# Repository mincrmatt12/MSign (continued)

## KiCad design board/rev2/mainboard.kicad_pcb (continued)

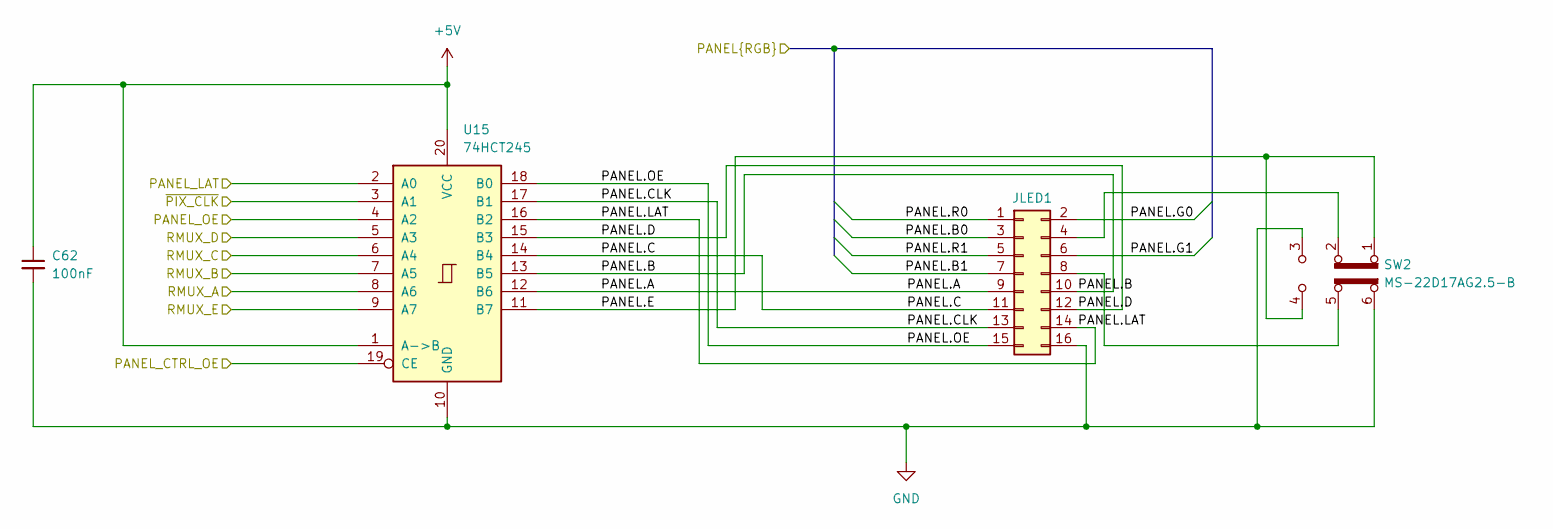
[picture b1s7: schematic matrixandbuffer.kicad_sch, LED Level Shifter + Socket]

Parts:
C62: 100nF; C_0402_1005Metric; Part CL05B104KB54PNC; LCSC C307331
JLED1: Conn_02x08_Counter_Clockwise; IDC-Header_2x08_P2.54mm_Vertical
SW2: MS-22D17AG2.5-B; SW-SMD_MS-22D17AG2.5; Part MS-22D17AG2.5-B; LCSC C20611671
U15: 74HCT245; TSSOP-20_4.4x6.5mm_P0.65mm; Part 74HCT245PW,118; LCSC C5980

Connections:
+5V: C62.1, U15.1 (A->B), U15.20 (VCC); also elsewhere on the board
/Decoder/PANELA.B0: JLED1.3; also elsewhere on the board
/Decoder/PANELA.B1: JLED1.7; also elsewhere on the board
/Decoder/PANELA.G0: JLED1.2; also elsewhere on the board
/Decoder/PANELA.G1: JLED1.6; also elsewhere on the board
/Decoder/PANELA.R0: JLED1.1; also elsewhere on the board
/Decoder/PANELA.R1: JLED1.5; also elsewhere on the board
/Decoder/PANEL_RGB_OE: U15.19 (CE); also elsewhere on the board
/Display MCU/PANEL_LAT: U15.2 (A0); also elsewhere on the board
/Display MCU/PANEL_OE: U15.4 (A2); also elsewhere on the board
/Display MCU/RMUX_A: U15.8 (A6); also elsewhere on the board
/Display MCU/RMUX_B: U15.7 (A5); also elsewhere on the board
/Display MCU/RMUX_C: U15.6 (A4); also elsewhere on the board
/Display MCU/RMUX_D: U15.5 (A3); also elsewhere on the board
/Display MCU/RMUX_E: U15.9 (A7); also elsewhere on the board
/Display MCU/~PIX_CLK: U15.3 (A1); also elsewhere on the board
/LED Connection A/PANEL.A: JLED1.9, U15.12 (B6)
/LED Connection A/PANEL.B: JLED1.10, U15.13 (B5)
/LED Connection A/PANEL.C: JLED1.11, U15.14 (B4)
/LED Connection A/PANEL.CLK: JLED1.13, U15.17 (B1)
/LED Connection A/PANEL.D: JLED1.12, U15.15 (B3)
/LED Connection A/PANEL.E: SW2.1 (A), SW2.4 (A), U15.11 (B7)
/LED Connection A/PANEL.LAT: JLED1.14, U15.16 (B2)
/LED Connection A/PANEL.OE: JLED1.15, U15.18 (B0)
GND: C62.2, JLED1.16, SW2.3 (C), SW2.6 (C), U15.10 (GND); also elsewhere on the board
unnamed: JLED1.4, SW2.2 (B)
unnamed: JLED1.8, SW2.5 (B)

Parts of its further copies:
C63: 100nF; C_0402_1005Metric; Part CL05B104KB54PNC; LCSC C307331
JLED2: Conn_02x08_Counter_Clockwise; IDC-Header_2x08_P2.54mm_Vertical
SW3: MS-22D17AG2.5-B; SW-SMD_MS-22D17AG2.5; Part MS-22D17AG2.5-B; LCSC C20611671
U16: 74HCT245; TSSOP-20_4.4x6.5mm_P0.65mm; Part 74HCT245PW,118; LCSC C5980

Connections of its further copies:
+5V: C63.1, U16.1 (A->B), U16.20 (VCC); also elsewhere on the board
/Decoder/PANELB.B0: JLED2.3; also elsewhere on the board
/Decoder/PANELB.B1: JLED2.7; also elsewhere on the board
/Decoder/PANELB.G0: JLED2.2; also elsewhere on the board
/Decoder/PANELB.G1: JLED2.6; also elsewhere on the board
/Decoder/PANELB.R0: JLED2.1; also elsewhere on the board
/Decoder/PANELB.R1: JLED2.5; also elsewhere on the board
/Decoder/PANEL_RGB_OE: U16.19 (CE); also elsewhere on the board
/Display MCU/PANEL_LAT: U16.2 (A0); also elsewhere on the board
/Display MCU/PANEL_OE: U16.4 (A2); also elsewhere on the board
/Display MCU/RMUX_A: U16.8 (A6); also elsewhere on the board
/Display MCU/RMUX_B: U16.7 (A5); also elsewhere on the board
/Display MCU/RMUX_C: U16.6 (A4); also elsewhere on the board
/Display MCU/RMUX_D: U16.5 (A3); also elsewhere on the board
/Display MCU/RMUX_E: U16.9 (A7); also elsewhere on the board
/Display MCU/~PIX_CLK: U16.3 (A1); also elsewhere on the board
/LED Connection B/PANEL.A: JLED2.9, U16.12 (B6)
/LED Connection B/PANEL.B: JLED2.10, U16.13 (B5)
/LED Connection B/PANEL.C: JLED2.11, U16.14 (B4)
/LED Connection B/PANEL.CLK: JLED2.13, U16.17 (B1)
/LED Connection B/PANEL.D: JLED2.12, U16.15 (B3)
/LED Connection B/PANEL.E: SW3.1 (A), SW3.4 (A), U16.11 (B7)
/LED Connection B/PANEL.LAT: JLED2.14, U16.16 (B2)
/LED Connection B/PANEL.OE: JLED2.15, U16.18 (B0)
GND: C63.2, JLED2.16, SW3.3 (C), SW3.6 (C), U16.10 (GND); also elsewhere on the board
unnamed: JLED2.4, SW3.2 (B)
unnamed: JLED2.8, SW3.5 (B)

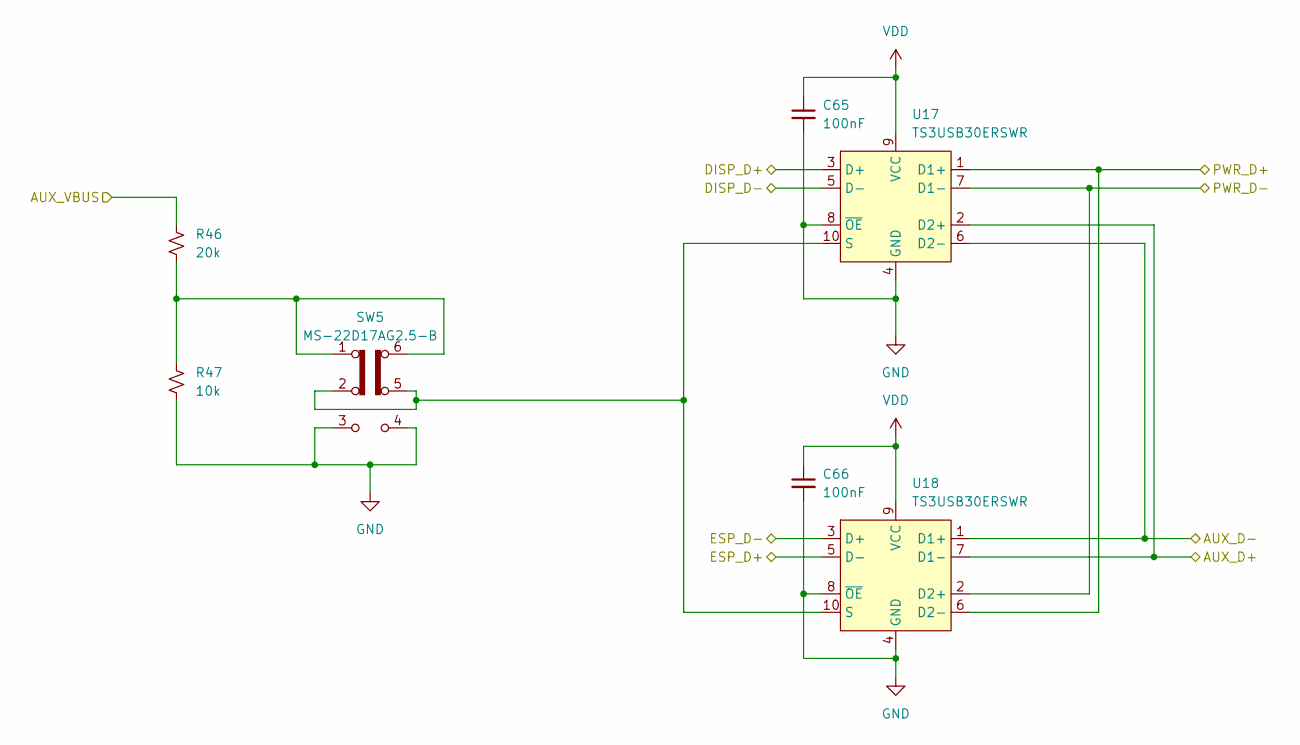
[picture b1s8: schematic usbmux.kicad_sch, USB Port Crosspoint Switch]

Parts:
C65, C66: 100nF; C_0402_1005Metric; Part CL05B104KB54PNC; LCSC C307331
R46: 20k; R_0603_1608Metric; Part 0603WAF2002T5E; LCSC C4184
R47: 10k; R_0805_2012Metric; Part 0805W8F1002T5E; LCSC C17414
SW5: MS-22D17AG2.5-B; SW-SMD_MS-22D17AG2.5; Part MS-22D17AG2.5-B; LCSC C20611671
U17, U18: TS3USB30ERSWR; UQFN-10_1.4x1.8mm_P0.4mm; Part TS3USB30ERSWR; LCSC C73880

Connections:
/Display MCU/USB_D+: U17.3 (D+); also elsewhere on the board
/Display MCU/USB_D-: U17.5 (D-); also elsewhere on the board
/Peripherals/AUX_USB_D+: U17.2 (D2+), U18.7 (D1-); also elsewhere on the board
/Peripherals/AUX_USB_D-: U17.6 (D2-), U18.1 (D1+); also elsewhere on the board
/Peripherals/AUX_USB_VBUS: R46.1; also elsewhere on the board
/Power/USB_D+: U17.1 (D1+), U18.6 (D2-); also elsewhere on the board
/Power/USB_D-: U17.7 (D1-), U18.2 (D2+); also elsewhere on the board
/USB Mux/ESP_D+: U18.5 (D-); also elsewhere on the board
/USB Mux/ESP_D-: U18.3 (D+); also elsewhere on the board
GND: C65.2, C66.2, R47.2, SW5.3 (C), SW5.4 (A), U17.4 (GND), U17.8 (~OE), U18.4 (GND), U18.8 (~OE); also elsewhere on the board
unnamed: R46.2, R47.1, SW5.1 (A), SW5.6 (C)
unnamed: SW5.2 (B), SW5.5 (B), U17.10 (S), U18.10 (S)
VDD: C65.1, C66.1, U17.9 (VCC), U18.9 (VCC); also elsewhere on the board

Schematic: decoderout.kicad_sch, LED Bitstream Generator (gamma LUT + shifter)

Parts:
C58, C59: 100nF; C_0402_1005Metric; Part CL05B104KB54PNC; LCSC C307331
R17, R24, R25, R26, R27, R28, R29, R30: 1k; R_0402_1005Metric; Part 0402WGF1001TCE; LCSC C11702
U11: IS61LV256AL; TSOP-28_L11.8-W8.0-P0.55-LS13.4-L; Part IS61LV256AL-10TLI; LCSC C412837
U12: 74AHCT595; TSSOP-16_4.4x5mm_P0.65mm; Part 74AHCT595T16-13; LCSC C460504

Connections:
+5V: C59.1, U12.10 (~SRCLR), U12.16 (VCC); also elsewhere on the board
/Decoder/MEMA_WE: U11.27 (~WE); also elsewhere on the board
/Decoder/MEM_A13: U11.21 (A10); also elsewhere on the board
/Decoder/MEM_IO: R17.2; also elsewhere on the board
/Decoder/Output Stage A/PIX_CNT_Q0: U11.26 (A13); also elsewhere on the board
/Decoder/Output Stage A/PIX_CNT_Q1: U11.25 (A8); also elsewhere on the board
/Decoder/Output Stage A/PIX_CNT_Q2: U11.24 (A9); also elsewhere on the board
/Decoder/Output Stage A/PIX_CNT_Q3: U11.23 (A11); also elsewhere on the board
/Decoder/Output Stage A/PIX_RGB_Q0: U11.1 (A14); also elsewhere on the board
/Decoder/Output Stage A/PIX_RGB_Q1: U11.2 (A12); also elsewhere on the board
/Decoder/PANELA.B0: U12.2 (QC); also elsewhere on the board
/Decoder/PANELA.B1: U12.5 (QF); also elsewhere on the board
/Decoder/PANELA.G0: U12.1 (QB); also elsewhere on the board
/Decoder/PANELA.G1: U12.4 (QE); also elsewhere on the board
/Decoder/PANELA.R0: U12.15 (QA); also elsewhere on the board
/Decoder/PANELA.R1: U12.3 (QD); also elsewhere on the board
/Decoder/PANEL_RGB_OE: U12.13 (~OE); also elsewhere on the board
/Decoder/PIX_CLK: U12.12 (RCLK); also elsewhere on the board
/Decoder/PIX_MEM_PA0: U11.10 (A0); also elsewhere on the board
/Decoder/PIX_MEM_PA1: U11.9 (A1); also elsewhere on the board
/Decoder/PIX_MEM_PA2: U11.8 (A2); also elsewhere on the board
/Decoder/PIX_MEM_PA3: U11.7 (A3); also elsewhere on the board
/Decoder/PIX_MEM_PA4: U11.6 (A4); also elsewhere on the board
/Decoder/PIX_MEM_PA5: U11.5 (A5); also elsewhere on the board
/Decoder/PIX_MEM_PA6: U11.4 (A6); also elsewhere on the board
/Decoder/PIX_MEM_PA7: U11.3 (A7); also elsewhere on the board
/Decoder/RGB_CLK: U12.11 (SRCLK); also elsewhere on the board
GND: C58.1, C59.2, R24.2, R25.2, R26.2, R27.2, R28.2, R29.2, R30.2, U11.14 (GND), U11.20 (~CE), U11.22 (~OE), U12.8 (GND); also elsewhere on the board
unnamed: R17.1, U11.11 (I/O0), U12.14 (SER)
unnamed: R24.1, U11.12 (I/O1)
unnamed: R25.1, U11.13 (I/O2)
unnamed: R26.1, U11.15 (I/O3)
unnamed: R27.1, U11.16 (I/O4)
unnamed: R28.1, U11.17 (I/O5)
unnamed: R29.1, U11.18 (I/O6)
unnamed: R30.1, U11.19 (I/O7)
VDD: C58.2, U11.28 (VDD); also elsewhere on the board

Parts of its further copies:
C60, C61: 100nF; C_0402_1005Metric; Part CL05B104KB54PNC; LCSC C307331
R32, R33, R34, R35, R36, R37, R38, R52: 1k; R_0402_1005Metric; Part 0402WGF1001TCE; LCSC C11702
U13: IS61LV256AL; TSOP-28_L11.8-W8.0-P0.55-LS13.4-L; Part IS61LV256AL-10TLI; LCSC C412837
U14: 74AHCT595; TSSOP-16_4.4x5mm_P0.65mm; Part 74AHCT595T16-13; LCSC C460504

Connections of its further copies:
+5V: C61.1, U14.10 (~SRCLR), U14.16 (VCC); also elsewhere on the board
/Decoder/MEMB_WE: U13.27 (~WE); also elsewhere on the board
/Decoder/MEM_A13: U13.21 (A10); also elsewhere on the board
/Decoder/MEM_IO: R52.2; also elsewhere on the board
/Decoder/Output Stage A/PIX_CNT_Q0: U13.26 (A13); also elsewhere on the board
/Decoder/Output Stage A/PIX_CNT_Q1: U13.25 (A8); also elsewhere on the board
/Decoder/Output Stage A/PIX_CNT_Q2: U13.24 (A9); also elsewhere on the board
/Decoder/Output Stage A/PIX_CNT_Q3: U13.23 (A11); also elsewhere on the board
/Decoder/Output Stage A/PIX_RGB_Q0: U13.1 (A14); also elsewhere on the board
/Decoder/Output Stage A/PIX_RGB_Q1: U13.2 (A12); also elsewhere on the board
/Decoder/PANELB.B0: U14.2 (QC); also elsewhere on the board
/Decoder/PANELB.B1: U14.5 (QF); also elsewhere on the board
/Decoder/PANELB.G0: U14.1 (QB); also elsewhere on the board
/Decoder/PANELB.G1: U14.4 (QE); also elsewhere on the board
/Decoder/PANELB.R0: U14.15 (QA); also elsewhere on the board
/Decoder/PANELB.R1: U14.3 (QD); also elsewhere on the board
/Decoder/PANEL_RGB_OE: U14.13 (~OE); also elsewhere on the board
/Decoder/PIX_CLK: U14.12 (RCLK); also elsewhere on the board
/Decoder/PIX_MEM_PB0: U13.10 (A0); also elsewhere on the board
/Decoder/PIX_MEM_PB1: U13.9 (A1); also elsewhere on the board
/Decoder/PIX_MEM_PB2: U13.8 (A2); also elsewhere on the board
/Decoder/PIX_MEM_PB3: U13.7 (A3); also elsewhere on the board
/Decoder/PIX_MEM_PB4: U13.6 (A4); also elsewhere on the board
/Decoder/PIX_MEM_PB5: U13.5 (A5); also elsewhere on the board
/Decoder/PIX_MEM_PB6: U13.4 (A6); also elsewhere on the board
/Decoder/PIX_MEM_PB7: U13.3 (A7); also elsewhere on the board
/Decoder/RGB_CLK: U14.11 (SRCLK); also elsewhere on the board
GND: C60.1, C61.2, R32.2, R33.2, R34.2, R35.2, R36.2, R37.2, R38.2, U13.14 (GND), U13.20 (~CE), U13.22 (~OE), U14.8 (GND); also elsewhere on the board
unnamed: R52.1, U13.11 (I/O0), U14.14 (SER)
unnamed: R32.1, U13.12 (I/O1)
unnamed: R33.1, U13.13 (I/O2)
unnamed: R34.1, U13.15 (I/O3)
unnamed: R35.1, U13.16 (I/O4)
unnamed: R36.1, U13.17 (I/O5)
unnamed: R37.1, U13.18 (I/O6)
unnamed: R38.1, U13.19 (I/O7)
VDD: C60.2, U13.28 (VDD); also elsewhere on the board

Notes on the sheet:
Gamma correction table (PIX_MEM)

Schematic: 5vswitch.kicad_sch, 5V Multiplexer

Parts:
C11: 1uF; C_0603_1608Metric; Part CL10A105KB8NNNC; LCSC C15849
C12, C15: 100nF; C_0402_1005Metric; Part CL05B104KB54PNC; LCSC C307331
C13: 2.2nF; C_0603_1608Metric; Part 0603B222K500NT; LCSC C1604
C14: 8.2nF; C_0603_1608Metric; Part 0603B822K500NT; LCSC C1322360
C16: 10uF; C_1206_3216Metric; Part CL31A106KBHNNNE; LCSC C13585
C17: 220uF; CP_Radial_D8.0mm_P3.50mm; Part ERS1VM221F12OT; LCSC C106697
Q1: WSD40120DN56G; DFN-8_L4.9-W6.0-P1.27-LS6.1-BL; Part WSD40120DN56G; LCSC C507088
Q2: 2N7002; SOT-23; Part 2N7002; LCSC C8545
R3: 10k; R_0402_1005Metric; Part 0402WGF1002TCE; LCSC C25744
R4: 510; R_0603_1608Metric; Part 0603WAF5100T5E; LCSC C23193
R5: 1.2k; R_0805_2012Metric; Part 0805W8F1201T5E; LCSC C17379
R6: 470k; R_0805_2012Metric; Part 0805W8F4703T5E; LCSC C17709
R7: 150k; R_0805_2012Metric; Part 0805W8F1503T5E; LCSC C17470
U3: TPS259472A; VQFN-10_L2.0-W2.0-P0.45-TL; Part TPS259472ARPWR; LCSC C3662789
U4: LM5050-1; TSOT-23-6; Part LM5050MKX-1/NOPB; LCSC C473393

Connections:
+5V: C16.1, C17.1, Q1.3 (D), R6.1, U3.6 (OUT), U4.6 (OUT); also elsewhere on the board
/Power MCU/DISC_5VREG: Q2.1 (G); also elsewhere on the board
/Power MCU/EN_5VREG: U4.3 (OFF); also elsewhere on the board
/Power MCU/EN_VBUS: R3.1, U3.1 (EN_UVLO); also elsewhere on the board
/Power MCU/VBUS_IMEAS: R5.1, U3.9 (ILM); also elsewhere on the board
/Power MCU/VBUS_PGOOD: U3.3 (PG); also elsewhere on the board
/Power/5V_REG: C15.1, Q1.1 (S), Q2.3 (D), U4.1 (VS), U4.4 (IN); also elsewhere on the board
/Power/VBUS: C11.1, C12.1, U3.5 (IN); also elsewhere on the board
GND: C11.2, C12.2, C13.2, C14.2, C15.2, C16.2, C17.2, R3.2, R4.2, R5.2, R7.2, U3.8 (GND), U4.2 (GND); also elsewhere on the board
unnamed: Q1.2 (G), U4.5 (GATE)
unnamed: Q2.2 (S), R4.1
unnamed: C13.1, U3.10 (ITIMER)
unnamed: R6.2, R7.1, U3.4 (PGTH)
unnamed: C14.1, U3.7 (dVdt)

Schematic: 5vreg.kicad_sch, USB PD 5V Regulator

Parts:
C18: 150uF; CP_Radial_D8.0mm_P3.50mm; Part ERS1VM151F12OT; LCSC C106696
C19, C20, C22: 4.7uF; C_1206_3216Metric; Part 1206B475K500NT; LCSC C29823
C21, C24, C25, C71: 100nF; C_0402_1005Metric; Part CL05B104KB54PNC; LCSC C307331
C23: 1uF; C_0603_1608Metric; Part CL10A105KB8NNNC; LCSC C15849
C26, C27, C28, C29, C30, C31, C32, C33: 47uF; C_1206_3216Metric; Part CL31A476MPHNNNE; LCSC C96123
L2: 1uH; L_Cenker_CKST1707; Part CKST1707-1uH/M; LCSC C5292052
NT1, NT2: NetTie_2; NetTie-2_SMD_Pad0.5mm
R8: 10k; R_0402_1005Metric; Part 0402WGF1002TCE; LCSC C25744
R9: 3.3k; R_0402_1005Metric; Part 0402WGF3301TCE; LCSC C25890
R10: 2.2; R_0603_1608Metric; Part 0603WAF220KT5E; LCSC C22939
TP7: TestPoint; TestPoint_Pad_D1.0mm
U5: SiC451; POWERPAK_MLP34-57_VIS; Part SIC451ED-T1-GE3; LCSC C1852144

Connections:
/Power MCU/5V_REG_SCL: U5.20 (SCL); also elsewhere on the board
/Power MCU/5V_REG_SDA: U5.19 (SDA); also elsewhere on the board
/Power MCU/5V_REG_SMBA: U5.18 (SALERT); also elsewhere on the board
/Power/5V Reg/VSEN+: NT1.1, U5.12 (VSEN+)
/Power/5V Reg/VSEN-: NT2.1, U5.11 (VSEN-)
/Power/5V_REG: C25.1, C26.1, C27.1, C28.1, C29.1, C30.1, C31.1, C32.1, C33.1, L2.2, NT1.2; also elsewhere on the board
/Power/VBUS: C18.1, C19.1, C20.1, C21.1, C71.1, U5.1 (PVIN), U5.23 (VIN); also elsewhere on the board
GND: C18.2, C19.2, C20.2, C21.2, C22.2, C23.2, C25.2, C26.2, C27.2, C28.2, C29.2, C30.2, C31.2, C32.2, C33.2, C71.2, NT2.2, R8.2, R9.2, TP7.1 (1_1), U5.7 (AGND), U5.15 (VSET), U5.21 (EN), U5.32 (PGND); also elsewhere on the board
unnamed: C24.2, R10.1
unnamed: R8.1, U5.14 (ADDR)
unnamed: R10.2, U5.6 (BOOT)
unnamed: C24.1, U5.4 (PHASE)
unnamed: C22.1, U5.24 (PVCC)
unnamed: R9.1, U5.17 (RT/SYNC)
unnamed: L2.1, U5.26 (SW)
unnamed: C23.1, U5.22 (VDD)

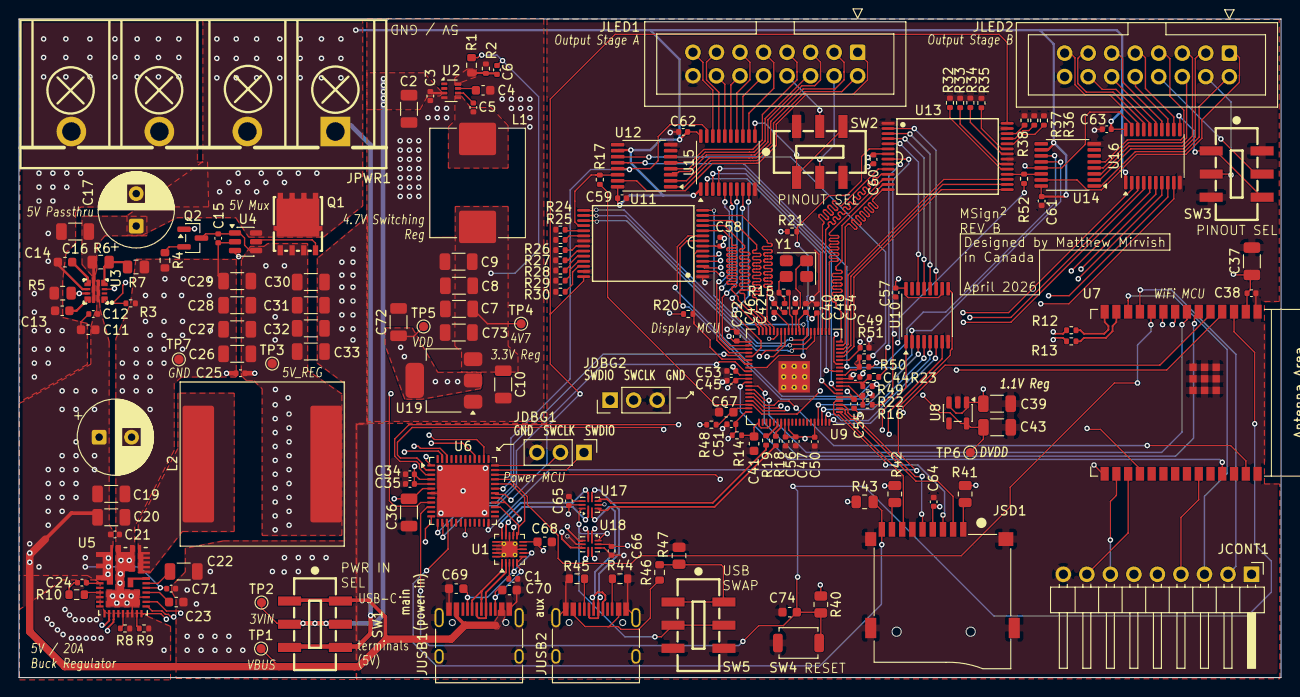
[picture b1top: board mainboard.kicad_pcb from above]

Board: 4 copper layers, 136.2 x 71.1 mm, 170 parts (0 on the bottom side), 189 nets.

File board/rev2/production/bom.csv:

Designator,Footprint,Quantity,Value,LCSC Part #
"C1, C12, C15, C21, C24, C25, C3, C34, C35, C38, C44, C45, C46, C47, C48, C49, C5, C50, C51, C52, C53, C54, C55, C56, C57, C58, C59, C60, C61, C62, C63, C64, C65, C66, C71",0402,35,100nF,C307331 
"C10, C16, C2, C37, C72",1206,5,10uF,C13585
"C11, C23, C68, C74",0603,4,1uF,C15849
C13,0603,1,2.2nF,C1604
C14,0603,1,8.2nF,C1322360
C17,CP_Radial_D8.0mm_P3.50mm,1,220uF,C106697
C18,CP_Radial_D8.0mm_P3.50mm,1,150uF,C106696
"C19, C20, C22, C36, C39, C43",1206,6,4.7uF,C29823 
"C26, C27, C28, C29, C30, C31, C32, C33, C7, C73, C8, C9",1206,12,47uF,C96123
C4,0603,1,33nF,C21117
"C40, C42",0402,2,15pF,C1548
"C41, C67",0603,2,2.2uF,C23630
C6,0402,1,10pF,C32949
"C69, C70",0603,2,330pF,C1664
JCONT1,PinHeader_1x09_P2.54mm_Horizontal,1,Conn_01x09_Pin,
"JDBG1, JDBG2",PinHeader_1x03_P2.54mm_Vertical,2,Conn_01x03,
"JLED1, JLED2",IDC-Header_2x08_P2.54mm_Vertical,2,Conn_02x08_Counter_Clockwise,
JPWR1,CONN-TH_4P-P9.50_WJHB9500M-9.5-04P-13-00A,1,Screw_Terminal_01x02,C255007
JSD1,microSD_XUNPU_TF-115-BCP9,1,Micro_SD_Card_Det1,C720505
"JUSB1, JUSB2",USB_C_Receptacle_HRO_TYPE-C-31-M-12,2,USB_C_Receptacle_USB2.0_14P,C165948
L1,L_Chilisin_BMRF00101040,1,6.8uH,C7502775
L2,L_Cenker_CKST1707,1,1uH,C5292052
Q1,DFN-8_L4.9-W6.0-P1.27-LS6.1-BL,1,WSD40120DN56G,C507088
R1,0603,1,49.9k,C23184
R10,0603,1,2.2,C22939
"R12, R13, R18, R19",0402,4,22,C25092
R14,0402,1,10,C25077
"R15, R17, R24, R25, R26, R27, R28, R29, R30, R32, R33, R34, R35, R36, R37, R38, R52",0402,17,1k,C11702
"R16, R22, R23, R49, R50, R51",0402,6,33,C25105
"R2, R20, R21, R3, R8",0402,5,10k,C25744
R4,1206,1,100,C17901
"R40, R41, R42, R43, R47",0805,5,10k,C17414 
"R44, R45",0603,2,5.1k,C23186
R46,0603,1,20k,C4184
R48,0402,1,200,C25087
R5,0805,1,1.2k,C17379
R6,0805,1,470k,C17709
R7,0805,1,150k,C17470
R9,0402,1,3.3k,C25890
"SW1, SW2, SW3, SW5",SW-SMD_MS-22D17AG2.5,4,MS-22D28-G020,C20611671
SW4,SW_SPST_TS-1088-xR020,1,TS-1088-AR02016,C720477
"TP1, TP2, TP3, TP4, TP5, TP6, TP7",TestPoint_Pad_D1.0mm,7,TestPoint,
U1,WQFN-20-1EP_3x3mm_P0.4mm_EP1.7x1.7mm_ThermalVias,1,TPD6S300A,C2876380 
U10,TSSOP-16_4.4x5mm_P0.65mm,1,74VHC161,C7421276
"U11, U13",TSOP-28_L11.8-W8.0-P0.55-LS13.4-L,2,IS61LV256AL,C412837
"U12, U14",TSSOP-16_4.4x5mm_P0.65mm,2,74AHCT595,C460504
"U15, U16",TSSOP-20_4.4x6.5mm_P0.65mm,2,74HCT245,C5980
"U17, U18",UQFN-10_1.4x1.8mm_P0.4mm,2,TS3USB30ERSWR,C73880 
U19,SOT-223-3_TabPin2,1,LD1117AG-33-AA3-A-R,C71121
U2,SOT-583-8,1,TPS62933,C3200405
U3,VQFN-10_L2.0-W2.0-P0.45-TL,1,TPS259472A,C3662789
U4,TSOT-23-6,1,LM5050-1,C473393
U5,POWERPAK_MLP34-57_VIS,1,SiC451,C1852144
U6,QFN-48-1EP_7x7mm_P0.5mm_EP5.6x5.6mm,1,STM32G071CBUx,C529343
U7,ESP32-C6-WROOM-1,1,ESP32-C6-WROOM-1,C5366877
U8,SOT-23-5,1,TLV74311,C485147
U9,RP2350-QFN-80-1EP_10x10_P0.4mm_EP3.4x3.4mm_ThermalVias,1,RP2354B,C39843328
Y1,Crystal_SMD_3225-4Pin_3.2x2.5mm,1,ABM8-272-T3,C20625731

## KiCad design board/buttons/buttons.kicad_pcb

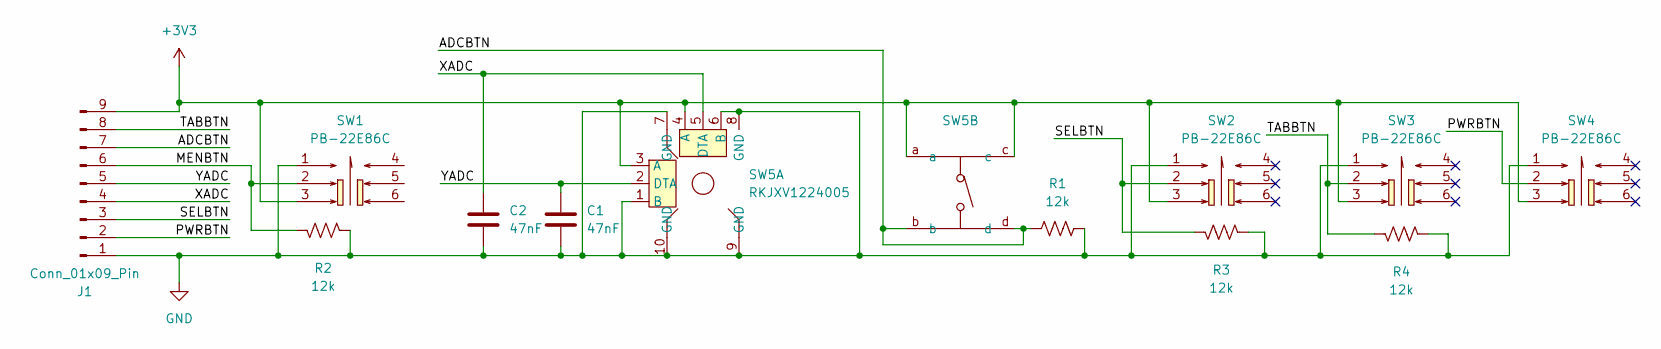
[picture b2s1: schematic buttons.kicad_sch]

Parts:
C1, C2: 47nF; C_0603_1608Metric; LCSC Part C1622
J1: Conn_01x09_Pin; PinHeader_1x09_P2.54mm_Horizontal
R1, R2, R3, R4: 12k; R_0402_1005Metric; LCSC Part C25752
SW1, SW2, SW3, SW4: PB-22E86C; SW-TH_6P-L8.45-W8.45-P2.50-LS5.5-BL; LCSC Part C2848957
SW5: RKJXV1224005; SW-TH_RKJXV1224005; LCSC Part C146170

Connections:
+3V3: J1.9, SW1.3, SW2.3, SW3.3, SW4.3, SW5.3 (A), SW5.4 (A), SW5.a, SW5.c
/ADCBTN: J1.7, R1.1, SW5.b, SW5.d
/MENBTN: J1.6, R2.2, SW1.2
/PWRBTN: J1.2, SW4.2
/SELBTN: J1.3, R3.2, SW2.2
/TABBTN: J1.8, R4.2, SW3.2
/XADC: C2.1, J1.4, SW5.5 (DTA)
/YADC: C1.1, J1.5, SW5.2 (DTA)
GND: C1.2, C2.2, J1.1, R1.2, R2.1, R3.1, R4.1, SW1.1, SW2.1, SW3.1, SW4.1, SW5.1 (B), SW5.6 (B), SW5.7 (GND), SW5.8 (GND), SW5.9 (GND), SW5.10 (GND)

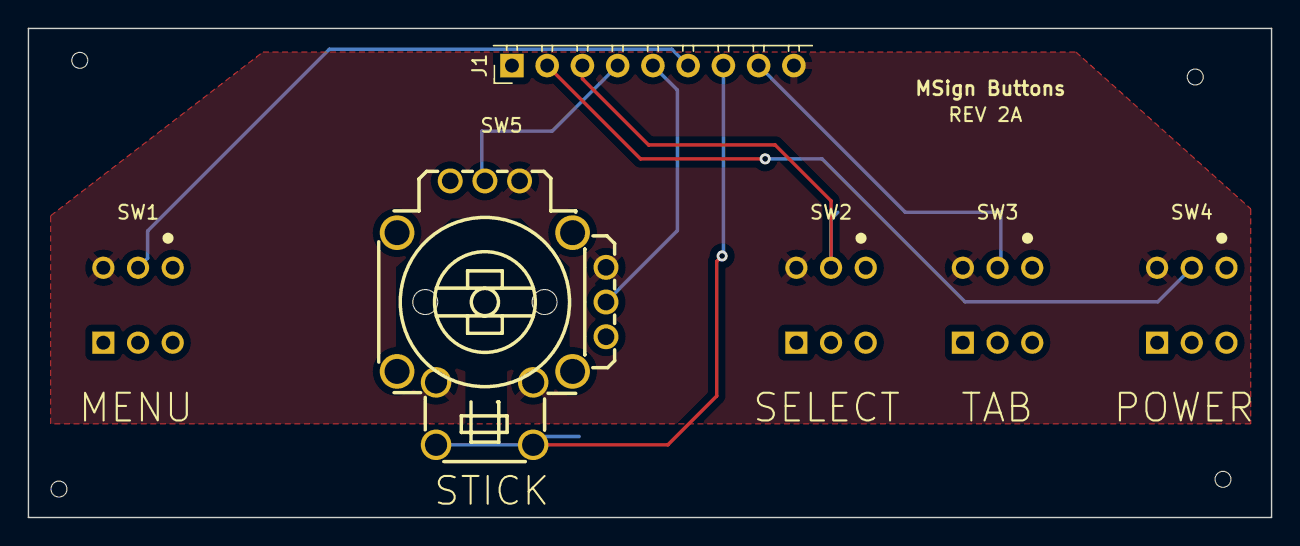
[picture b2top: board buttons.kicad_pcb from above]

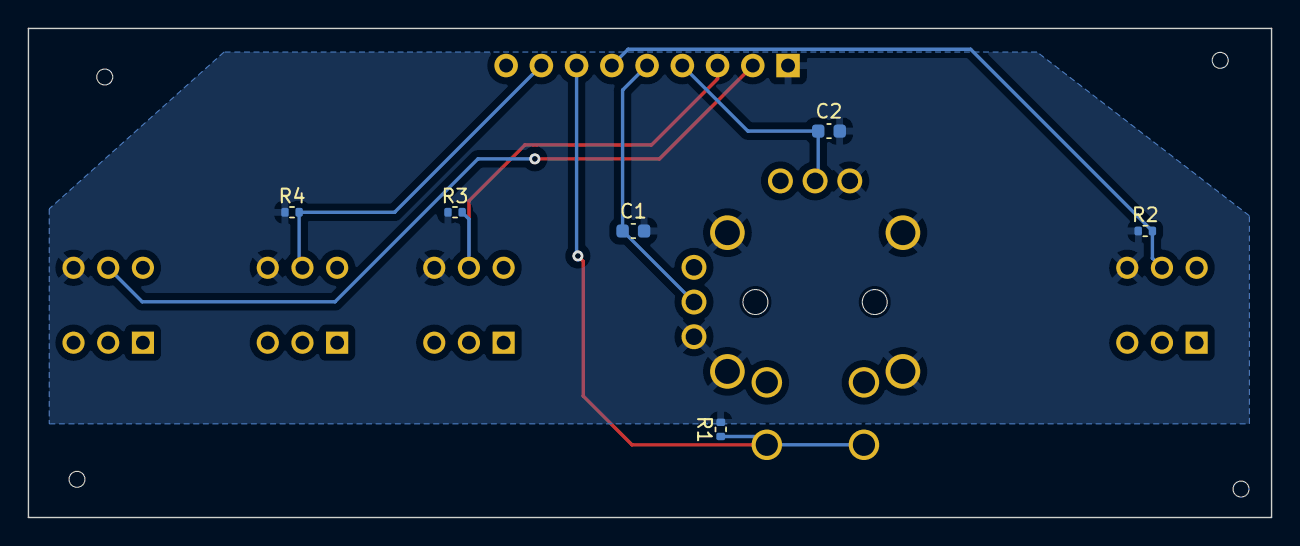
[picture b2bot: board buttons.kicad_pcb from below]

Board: 2 copper layers, 89.6 x 35.2 mm, 12 parts (6 on the bottom side), 9 nets.

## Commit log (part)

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2023-12-26 Add script to unpack a json dump with slotlib prettyprinting
2023-12-26 Sync octoprint on 409 case because update_slot() was going the nocopy route
2023-12-27 Add more outline text overloads
2023-12-27 Remove geocoding
2023-12-27 Fix template deduction on GCC 12
2023-12-27 Reopen file
2023-12-27 More sd error checking pt the third
    this time for writes not reads!
2023-12-27 Hide filename when no print job is loaded
2023-12-28 Fix octoprint grabber completion
    (from 0-100, not 0-1)
2023-12-28 Add printer icon animation
2023-12-28 Add new octoprint options to webui
2023-12-28 Scale bitmaps to dim - 1 instead of dim
    we want the pixels to occupy coordinates from [0, dim), so we
    need to multiply the 0.0-1.0 coords by dim - 1, not dim
2023-12-30 Adjust dupm queue timeout to 0 for requests from serial
    This prevents a deadlock of the form:
    - dupm queue fills
    - dupm waits for packet
    - serial gets a DATA_TEMP message
    - serial waits for 5 seconds for empty space in dupm
    - dupm wait timeout expires
2023-12-31 Implement analog stick
2023-12-31 Use up as virtual previous, not down
2023-12-31 Swap ADC pins with TAB/SEL buttons
    their original pins are not adc inputs. rev2 board will fix this if
    I ever manufacture it
2023-12-31 Ignore kicad lock files in board/
2023-12-31 Add joystick interaction to octoprint screen
    also speed up rendering hopefully with faster rounding
2023-12-31 Fix duplicated scroll table entry
2024-01-01 Add more fs validation in the octoprint bitmap handler
2024-01-01 Ensure restarting HTTP reconnects to try to avoid octoprint kicking us for being slow
2024-01-02 Use midnight as end of day for parcel est. delivery
2024-01-04 Document required fields
2024-01-04 Quantize times to <5minutes where applicable.
2024-01-05 Limit minutely data
2024-01-06 Add serial::interface.update_slot_at_inline
2024-01-06 Fix infinite loop in precip graph draw
2024-01-06 Resolve all interrupt handlers in log to names
2024-01-06 Ensure stm_crash target gets -O2 at least
2024-01-06 Fix missing sync after appending to summary buffer
    also wrong length calc
2024-01-06 Be less conservative in deeming precipitation "unlikely"
2024-01-06 Send grab task high watermark in metrics reports
2024-01-07 Adjust wording for "tomorrow night" when referring to next morning
2024-01-07 Fix rounding issues in bheap
    Problems resulting from the previous fix (now instead of bheap
    corruption, we had bheap infinite loops!)
2024-01-07 Remove erroneous public: in bheap method
    (was added for testing, forgot to remove)
2024-01-07 Add vendor/ to rgignore
2024-01-08 Fix missing "and" in summarizer
2024-01-09 Adjust interaction speeds in weather graph
2024-01-10 Adjust windy icon threshold
2024-01-10 Fix weathersummarizer fusing of unbounded minutely blocks
2024-01-12 Fix cfgserver typos
2024-01-12 Bump cfgserver to 0.1.5
2024-01-25 Ensure cache dir exists in yarn container
2024-02-03 Fix wtest argc check
2024-02-09 Ensure fused data does not limit precision in summaries
2024-02-13 Fix broken check for previous amt in summarizer
2024-02-13 Remove max_hourly_precision in favour of per-timespec precision
2024-03-11 Begin five-day forecast view
2024-03-11 Add five-day forecast view
2024-03-11 Fix arrows in fiveday view
2024-03-18 Add ESP8266 panic/crashlog saving
    After a fatal error, we write the crashlog contents (or at least
    the backtrace; the other PANIC() messages aren't captured at the moment)
    into RAM, then on the next boot we write that message to the SD card.
2024-03-18 Ensure no null bytes wind up in crash log files
2024-03-23 Ensure STM does not freeze after ESP crash during sleep
2024-04-19 Fix detection of likely/unlikely precipitation
2024-04-23 Use a heap-allocated larger file send buffer where possible
2024-06-07 Put minimum bound on precipitation probability when the icon is set
    This avoids a lot of the "rain starting in <5 minutes" summaries that
    go on perpetually despite the server-side icon assignments making
    physical sense.
2024-06-08 Halfhearted attempt to deal with hour 0 offset in minutes
    really should be plumbed through as_minutes()
2024-06-15 Add translate_messages to espweb
2024-06-16 Fix should_ignore_hourly_summary
2024-06-18 Revert broken fix in weathersummarizer
2024-06-24 Show parcel status when only icon is available
2024-06-24 Fix condition in parcels
2024-06-24 Fix alignment
2024-06-28 Remove unused class icons
    (used to be in tdsb grabber, no longer used)
2024-06-29 Store snow depth instead of speed on daily precip
2024-06-29 Add raw_timestamp to espweb
2024-07-03 Refactor parcel status matching
2024-07-03 Fix buggy weather data fuse
    Still obviously not considering the actual hour offset but meh.
2024-07-08 Remove unused vera_8 font
2024-07-10 Limit range on hourly precipitation to preserve precision
2024-07-11 Fix parcel long scroll flicker
2024-07-13 update buttons kicad project files after kicad 8
    some extra fields get generated... who knows?
2024-07-13 Remove libc dependency from stmboot
    Also doesn't link against libgcc, which is technically wrong but the
    bootloader is not meant to use any of the things libgcc fills anyways.
2024-07-14 Remove stm dependency on newlib
    The entirety of the stm codebase right now only relied on:
    - mem{move,cpy,set}: trivial to reimplement (even without
    optimizations, just using -O3 on a naive implementation generates
    suitable unrolling)
    - strlen & strncpy: also trivial to implement
    - strftime & gmtime_r: replaced with c++ quasi-time.h implementation
2024-07-14 Fix stm build scripts always regenerating stm.bin
2024-07-15 Fix out-of-bounds write in dupm
2024-07-15 Update ESP toolchain
    ARM: 13.3 -> (unchanged)
    ESP: 8.4.0 -> 13.2 (built from 8.4.0 newlib, 13.2 esp32 libstdc++ and debian GCC)
    Debian: bookworm -> trixie
2024-07-15 Fix dockerfile to work from an unpatched SDK
2024-07-22 Allow wildcard dirtag matches in ttc
2024-08-09 Add degree symbol to tahoma_9 font
2024-08-09 Enhance descriptions of weather graphs
    also using the new ° symbol in the font
2024-09-01 Add entry to clangd to remove charset override
    clang doesn't seem to like `cp1252` as a charset
2024-09-01 Adjust gamma from 2.6 to 2.45
    as an experiment
2024-09-07 Minor tweak in locking around slots::TTC_INFO
2024-10-01 Adjust colors on weather for fog
2024-10-01 Fix bug with e-notation in json parser
2024-10-01 Check for memory alloc fail in bearssl_supplicant
2024-10-01 Move lwip clone from savannah.nongnu to the github mirror
2024-10-11 Set wifi free heap threshold to 10k
2024-10-22 Try to re-init wifi after disconnect fail
2024-10-28 Upgrade js dependencies to appease dependabot
2024-10-28 actually call esp_wifi_connect in the reset code
2024-10-30 Fix weather graph occasionally showing negative wind
2024-11-10 Add fix for memory leak in sdk code
    When reconnecting to a WPA2-Enterprise network, the system can decide
    to cache on a reconnection attempt, in which case the EAP sm is not
    cleaned up and roughly 7k is leaked (well, it's referenced by a global
    so will not accumulate over multiple attempts, but still) as a result.
    This adds a few hacks to ensure the SDK code is told about key
    negotiation succeeding regardless - this is complicated by the fact that
2024-11-11 Cleanup TypedBlock helpers and add array size()
    uses requires to conditionally include methods instead of static
    asserts, far cleaner
    also adds a size() to return the array size of a pointer specialization
2024-11-20 Fix snow icon
2024-11-20 Discard GTFS updates if they are empty
    (using old information)
2024-11-20 Add clangd file for stm common
    fixes autocomplete by assuming a boring normal c++20 setup
    for the files which are completely standalone
2024-11-26 Avoid showing 0mm of snow if no accumulation, show rate instead
2024-11-27 Ensure enums with "negative" values get parsed by slotlib
2024-12-10 Add bitmask_of to slots.h
    and support in slotlib - used to mark bitmasks without using enum names
    (works better for multiple fields with same bitmask, like in new sccfg
    status reports)
2025-01-14 Set confgen to parse as c++20
2025-01-14 Fix incomplete refactor on sccfg
2025-01-18 Replace line_impl_low/high with a template
    (and also remove the redundant dx < 0/dy < 0 checks as we
    already swap the points natively)
2025-01-18 Add tailed block support to slotlib
    (bheap supports fixed-length header + dynamic trailer;
    only fixed types in slotlib atm)
2025-03-03 Unify draw::line low/high into a template
    also remove the redundant dx < 0 checks on the impl side
2025-03-03 Fix updates while sleeping
    (exits sleep for update)
2025-03-04 Avoid inlining fixed_t in octoprintbitmap
    (it's very large and would do better icached)
2025-03-05 Treat operational=false as disconnected in octoprint
2025-04-29 Avoid wind summaries with underwhelming wind
2025-04-29 Fix CI build due to newer xtensa gcc
    Pins ESP toolchian at gcc 13.2
    I do not feel like recreating the UNHOLY FUSION that is the
    newlib-libstdc++-xtensa-lx106-elf-13.2.0.tar.xz archive at the moment.
    (more importantly, it's based on the official ESP32 sources and they
    never released a 13.3 build).
2025-09-20 Upgrade toolchains in build
    ARM GCC: 13.2 -> debian build (14)
2025-10-14 Update ESP sdk
    fixes submodule urls in git, among other things
2025-10-18 Relax restrictions around ranged timespecs in summarizer
    improves situations like
    .##......... ##
    where you have a long uncertain tail and then a short gap, and
    then more precip; the summarizer instead takes center() in all cases
    which sounds dumb because it'll be measuring as if
    .####### ##
2025-10-23 Print finished text in green for octoprint
    also test change to Jenkins for included regions
2025-11-04 Fix three.js url
    yes i know esm is the right way to go nowadays; this code is ancient tho
2025-11-11 Add first chunk of rev2 PCB
    - power stage tentatively done
    - probably going to switch from sic951->sic451 with external
    inductor as it's far easier to get a hold of
    - still need to play with the eval boards for the sic951 which I
    have (i'd prefer to have the 451 but it's not in stock and i'm not
    paying for mouser shipping)
2025-11-11 remove sic951 --> start doing sic451
2025-11-11 Continue board work
    - move to rp2040, separate stm32g071 to do usb-c + aux ctrl IO
    - still cheaper lol with the cost of stm32s
    - more power reg stuff
2025-12-04 Bump @babel/runtime from 7.21.0 to 7.28.4 in /espweb
    Bumps [@babel/runtime](https://github.com/babel/babel/tree/HEAD/packages/babel-runtime) from 7.21.0 to 7.28.4.
    - [Release notes](https://github.com/babel/babel/releases)
    - [Changelog](https://github.com/babel/babel/blob/main/CHANGELOG.md)
    - [Commits](https://github.com/babel/babel/commits/v7.28.4/packages/babel-runtime)
    ---
    updated-dependencies:
2025-12-14 Continue board, assign caps/res, adjust for JLC availability
2025-12-15 Really finish rev2 board schematic
    - fix some more footprints
    - move to real SD card holder, for example
    - repair part numbers
    - add LCSC part refs to everything
    - add even more caps to the 3.3V reg output
    - really should use an LDO but meh it should be fine
2025-12-16 Add utf8 mode to jdump
2025-12-21 Abort webui cfg update if grab task is busy
    init can take a while, so this naturally ratelimits POST /config.json
2025-12-23 Show weather graph label for less time
2025-12-28 Layout more component blocks
    - regulators
    - mcus
    Still need to do the decoders + overall packing
2025-12-29 Fix cfgserver mimetype in metrics
2025-12-30 Use only one worker in cfgserver
    i forgot how crappy the metrics impl was lol
    should really make this use redis or something
2026-01-13 Steal patch from AUR to fix menuconfig
2026-01-22 Modernify readme requirements + bump copyright
2026-02-24 Bump lodash-es from 4.17.21 to 4.17.23 in /espweb
    Bumps lodash-es from 4.17.21 to 4.17.23.
    ---
    updated-dependencies:
    - dependency-name: lodash-es
    dependency-version: 4.17.23
    dependency-type: direct:production
2026-04-23 Add .history to gitignore (kicad 10)
2026-04-26 Add extra parameter changer to parcels page
2026-04-29 Track shipped time for progress bar in parcels
